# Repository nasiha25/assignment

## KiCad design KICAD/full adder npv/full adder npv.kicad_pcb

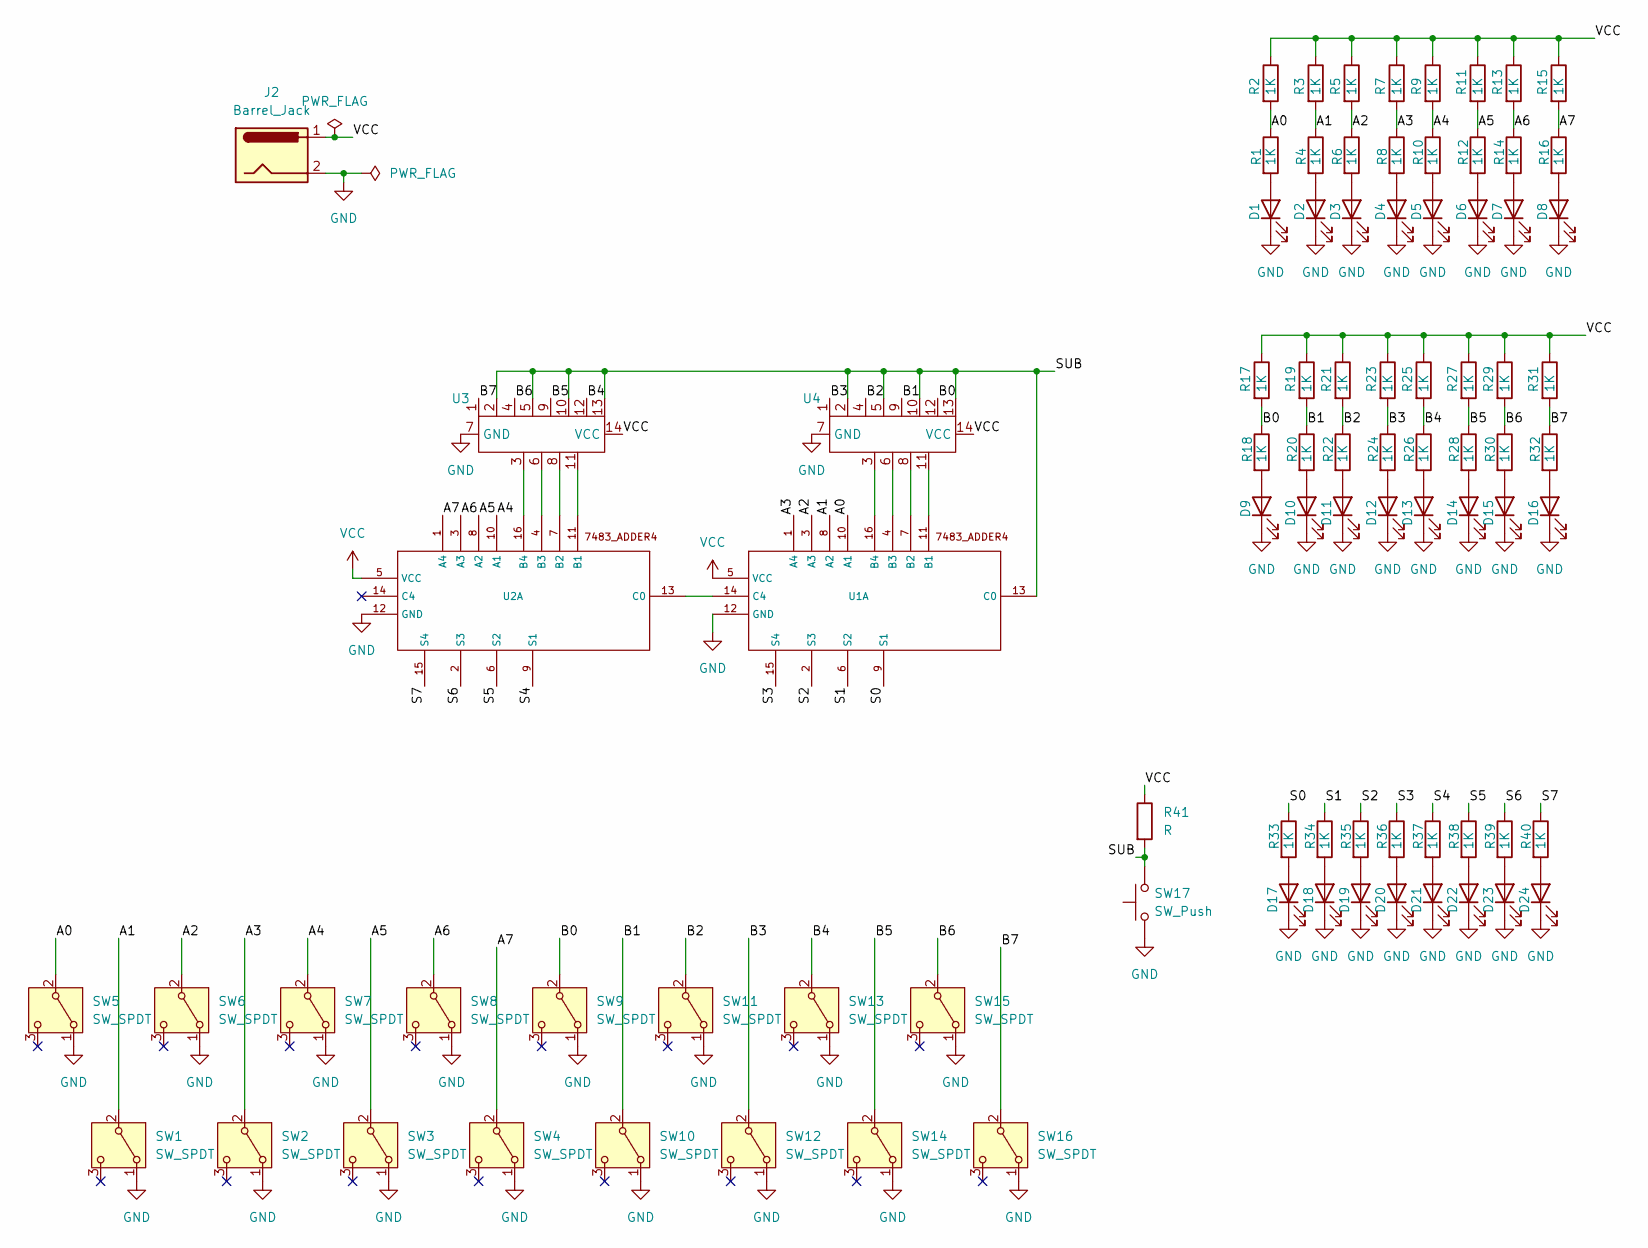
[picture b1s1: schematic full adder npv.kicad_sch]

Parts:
D1, D2, D3, D4, D5, D6, D7, D8, D9, D10, D11, D12, D13, D14, D15, D16, D17, D18, D19, D20, D21, D22, D23, D24: LED; LED_D3.0mm
J2: Barrel_Jack; BarrelJack_Horizontal
R1, R2, R3, R4, R5, R6, R7, R8, R9, R10, R11, R12, R13, R14, R15, R16, R17, R18, R19, R20, R21, R22, R23, R24, R25, R26, R27, R28, R29, R30, R31, R32, R33, R34, R35, R36, R37, R38, R39, R40: 1K; R_Axial_DIN0204_L3.6mm_D1.6mm_P5.08mm_Horizontal
R41: R; R_Axial_DIN0204_L3.6mm_D1.6mm_P5.08mm_Horizontal
SW1, SW2, SW3, SW4, SW5, SW6, SW7, SW8, SW9, SW10, SW11, SW12, SW13, SW14, SW15, SW16: SW_SPDT; switch1
SW17: SW_Push; switch1
U1, U2: DIP-16_W7.62mm
U3, U4: DIP-14_W7.62mm

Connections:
/A0: R1.1, R2.2, SW5.2 (B), U1.10 (A1)
/A1: R3.2, R4.1, SW1.2 (B), U1.8 (A2)
/A2: R5.2, R6.1, SW6.2 (B), U1.3 (A3)
/A3: R7.2, R8.1, SW2.2 (B), U1.1 (A4)
/A4: R9.2, R10.1, SW7.2 (B), U2.10 (A1)
/A5: R11.2, R12.1, SW3.2 (B), U2.8 (A2)
/A6: R13.2, R14.1, SW8.2 (B), U2.3 (A3)
/A7: R15.2, R16.1, SW4.2 (B), U2.1 (A4)
/B0: R17.2, R18.1, SW9.2 (B), U4.12
/B1: R19.2, R20.1, SW10.2 (B), U4.9
/B2: R21.2, R22.1, SW11.2 (B), U4.4
/B3: R23.2, R24.1, SW12.2 (B), U4.1
/B4: R25.2, R26.1, SW13.2 (B), U3.12
/B5: R27.2, R28.1, SW14.2 (B), U3.9
/B6: R29.2, R30.1, SW15.2 (B), U3.4
/B7: R31.2, R32.1, SW16.2 (B), U3.1
/S0: R33.1, U1.9 (S1)
/S1: R34.1, U1.6 (S2)
/S2: R35.1, U1.2 (S3)
/S3: R36.1, U1.15 (S4)
/S4: R37.1, U2.9 (S1)
/S5: R38.1, U2.6 (S2)
/S6: R39.1, U2.2 (S3)
/S7: R40.1, U2.15 (S4)
/SUB: R41.2, SW17.2, U1.13 (C0), U3.2, U3.5, U3.10, U3.13, U4.2, U4.5, U4.10, U4.13
GND: D1.1 (K), D2.1 (K), D3.1 (K), D4.1 (K), D5.1 (K), D6.1 (K), D7.1 (K), D8.1 (K), D9.1 (K), D10.1 (K), D11.1 (K), D12.1 (K), D13.1 (K), D14.1 (K), D15.1 (K), D16.1 (K), D17.1 (K), D18.1 (K), D19.1 (K), D20.1 (K), D21.1 (K), D22.1 (K), D23.1 (K), D24.1 (K), J2.2, SW1.1 (A), SW2.1 (A), SW3.1 (A), SW4.1 (A), SW5.1 (A), SW6.1 (A), SW7.1 (A), SW8.1 (A), SW9.1 (A), SW10.1 (A), SW11.1 (A), SW12.1 (A), SW13.1 (A), SW14.1 (A), SW15.1 (A), SW16.1 (A), SW17.1, U1.12 (GND), U2.12 (GND), U3.7 (GND), U4.7 (GND)
unnamed: D1.2 (A), R1.2
unnamed: D2.2 (A), R4.2
unnamed: D3.2 (A), R6.2
unnamed: D4.2 (A), R8.2
unnamed: D5.2 (A), R10.2
unnamed: D6.2 (A), R12.2
unnamed: D7.2 (A), R14.2
unnamed: D8.2 (A), R16.2
unnamed: D9.2 (A), R18.2
unnamed: D10.2 (A), R20.2
unnamed: D11.2 (A), R22.2
unnamed: D12.2 (A), R24.2
unnamed: D13.2 (A), R26.2
unnamed: D14.2 (A), R28.2
unnamed: D15.2 (A), R30.2
unnamed: D16.2 (A), R32.2
unnamed: D17.2 (A), R33.2
unnamed: D18.2 (A), R34.2
unnamed: D19.2 (A), R35.2
unnamed: D20.2 (A), R36.2
unnamed: D21.2 (A), R37.2
unnamed: D22.2 (A), R38.2
unnamed: D23.2 (A), R39.2
unnamed: D24.2 (A), R40.2
unnamed: U1.11 (B1), U4.11
unnamed: U1.7 (B2), U4.8
unnamed: U1.4 (B3), U4.6
unnamed: U1.16 (B4), U4.3
unnamed: U1.14 (C4), U2.13 (C0)
unnamed: U2.11 (B1), U3.11
unnamed: U2.7 (B2), U3.8
unnamed: U2.4 (B3), U3.6
unnamed: U2.16 (B4), U3.3
VCC: J2.1, R2.1, R3.1, R5.1, R7.1, R9.1, R11.1, R13.1, R15.1, R17.1, R19.1, R21.1, R23.1, R25.1, R27.1, R29.1, R31.1, R41.1, U1.5 (VCC), U2.5 (VCC), U3.14 (VCC), U4.14 (VCC)

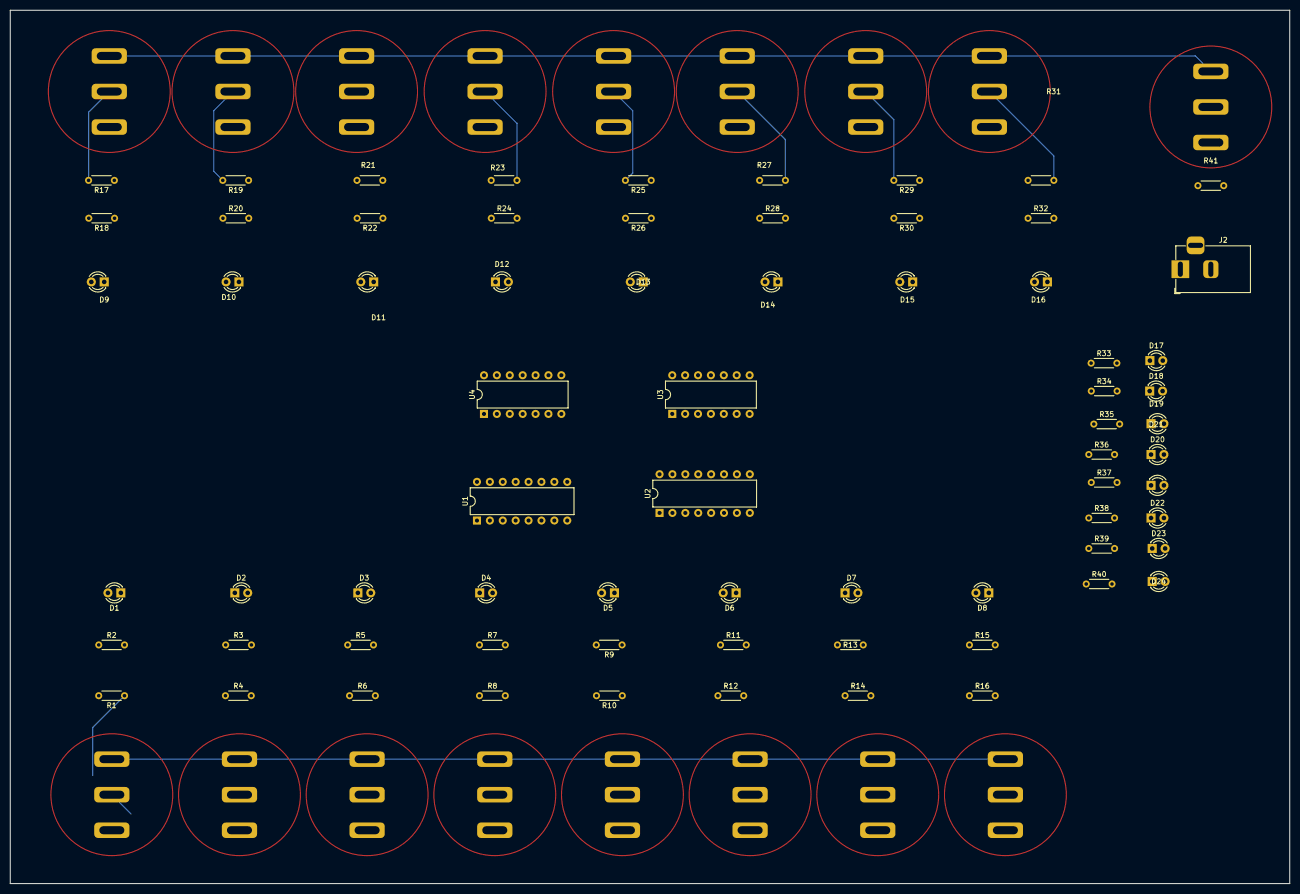
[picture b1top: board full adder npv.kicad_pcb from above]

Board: 2 copper layers, 252.0 x 172.0 mm, 87 parts (0 on the bottom side), 60 nets.

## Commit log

2025-11-24 ASSIGNMENT
